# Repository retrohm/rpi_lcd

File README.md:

rpi_lcd
=======

raspberry pi lcd status board design files

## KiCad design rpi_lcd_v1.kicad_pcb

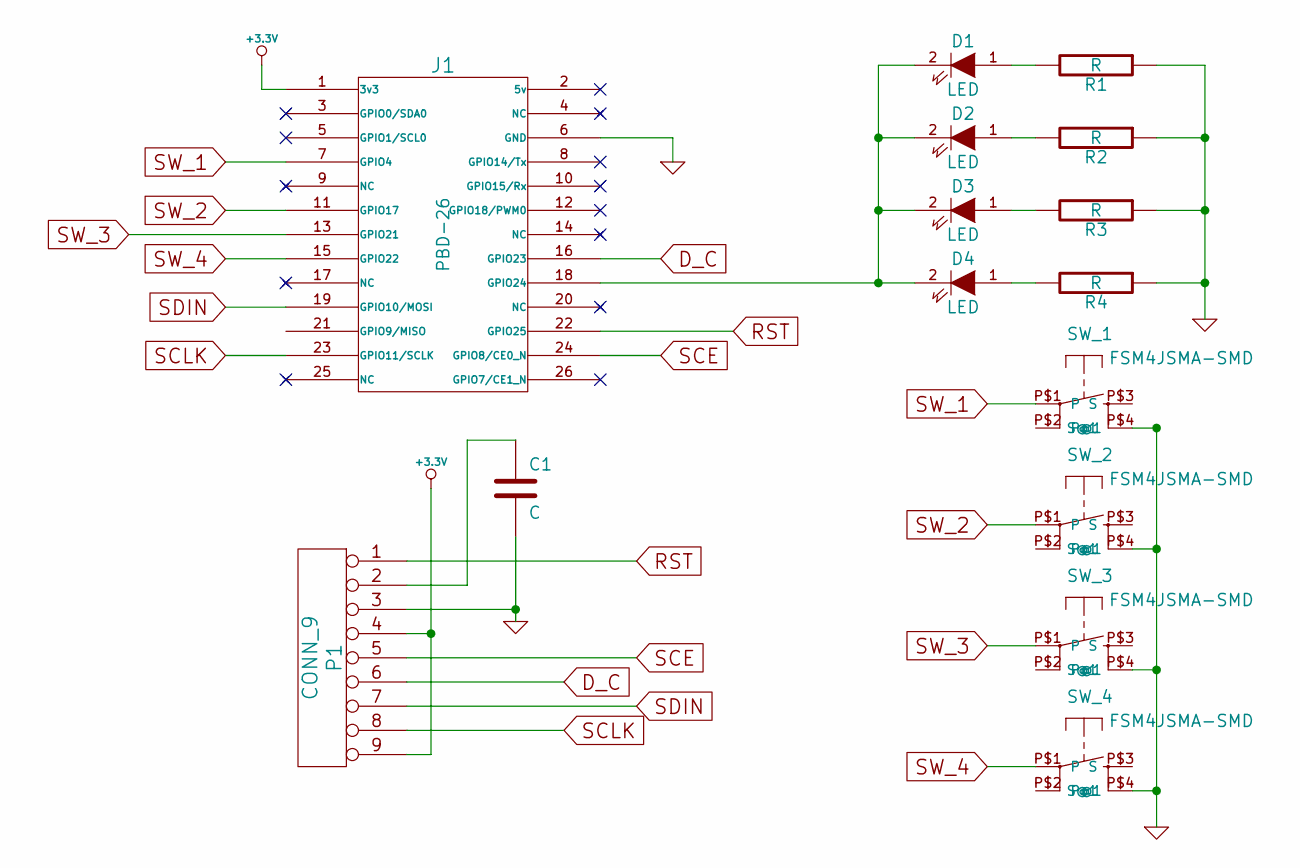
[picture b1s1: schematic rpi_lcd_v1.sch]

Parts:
C1: C
D1, D2, D3, D4: LED
J1: PBD-26
P1: CONN_9
R1, R2, R3, R4: R
SW_1, SW_2, SW_3, SW_4: FSM4JSMA-SMD; switch-misc-FSM4JSMA-SMD

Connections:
+3.3V: J1.1 (3v3), P1.4, P1.9
D_C: J1.16 (GPIO23), P1.6
GND: C1.2, J1.6 (GND), P1.3, R1.1, R2.1, R3.1, R4.1, SW_1.P$4 (S@1), SW_2.P$4 (S@1), SW_3.P$4 (S@1), SW_4.P$4 (S@1)
unnamed: C1.1, P1.2
unnamed: D1.2 (K), D2.2 (K), D3.2 (K), D4.2 (K), J1.18 (GPIO24)
unnamed: D3.1 (A), R3.2
unnamed: D4.1 (A), R4.2
unnamed: D1.1 (A), R1.2
unnamed: D2.1 (A), R2.2
RST: J1.22 (GPIO25), P1.1
SCE: J1.24 (GPIO8/CE0_N), P1.5
SCLK: J1.23 (GPIO11/SCLK), P1.8
SDIN: J1.19 (GPIO10/MOSI), P1.7
SW_1: J1.7 (GPIO4), SW_1.P$1
SW_2: J1.11 (GPIO17), SW_2.P$1
SW_3: J1.13 (GPIO21), SW_3.P$1
SW_4: J1.15 (GPIO22), SW_4.P$1

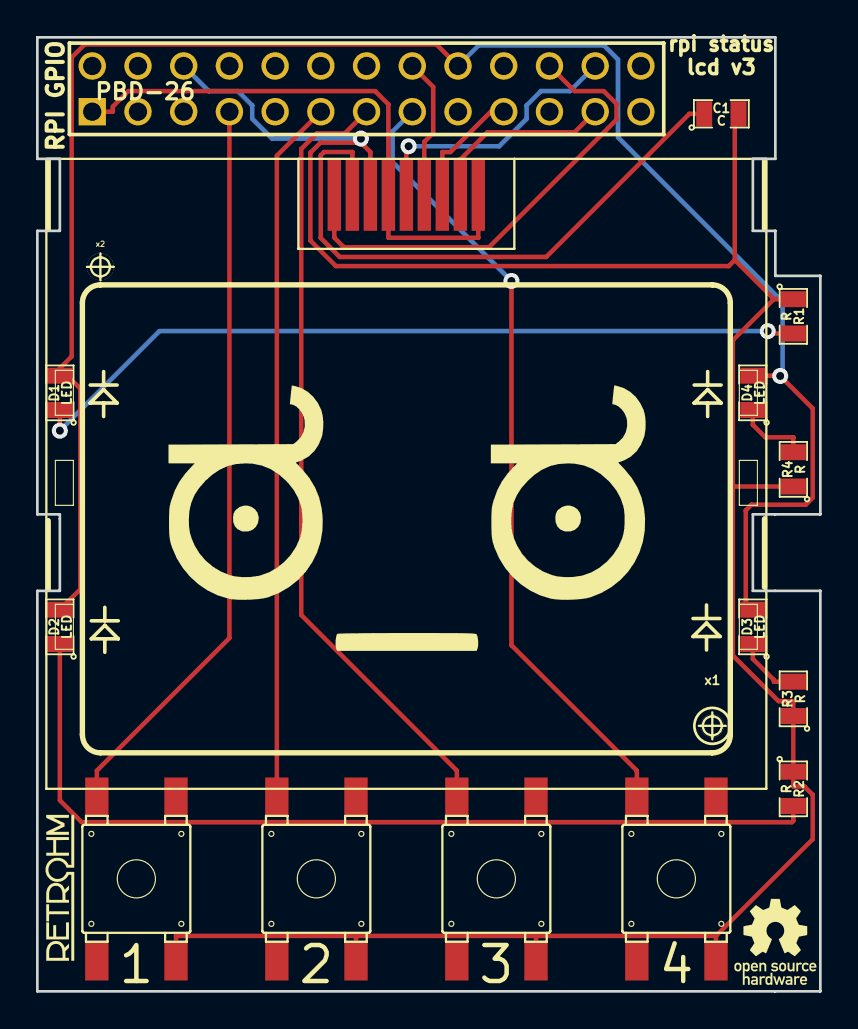
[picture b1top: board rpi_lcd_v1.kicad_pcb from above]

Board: 2 copper layers, 43.5 x 53.0 mm, 21 parts (0 on the bottom side), 17 nets.

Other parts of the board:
VAL: look_of_disapproval_scaled
VAL#2: bah
osh1: oshw-logo-200mil
rohm1: retrohm-logo-350mil
x1, x2: 1PIN_6mm

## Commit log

2013-04-05 Raspberry Pi Status LCD board WIP import
2013-04-13 Added led orientation silk
2013-04-13 Routed
2013-04-13 Add silk screen
2013-04-13 Added ground plane fill
2013-04-13 Add inkscape svg of back silk
2013-04-13 Added gerbers sent to oshpark
2013-04-13 Updated project file
2013-08-16 Fixed d/c line, fixed LED orientation
2013-10-04 Fixed back of board, plotted gerbers for oshpark order
